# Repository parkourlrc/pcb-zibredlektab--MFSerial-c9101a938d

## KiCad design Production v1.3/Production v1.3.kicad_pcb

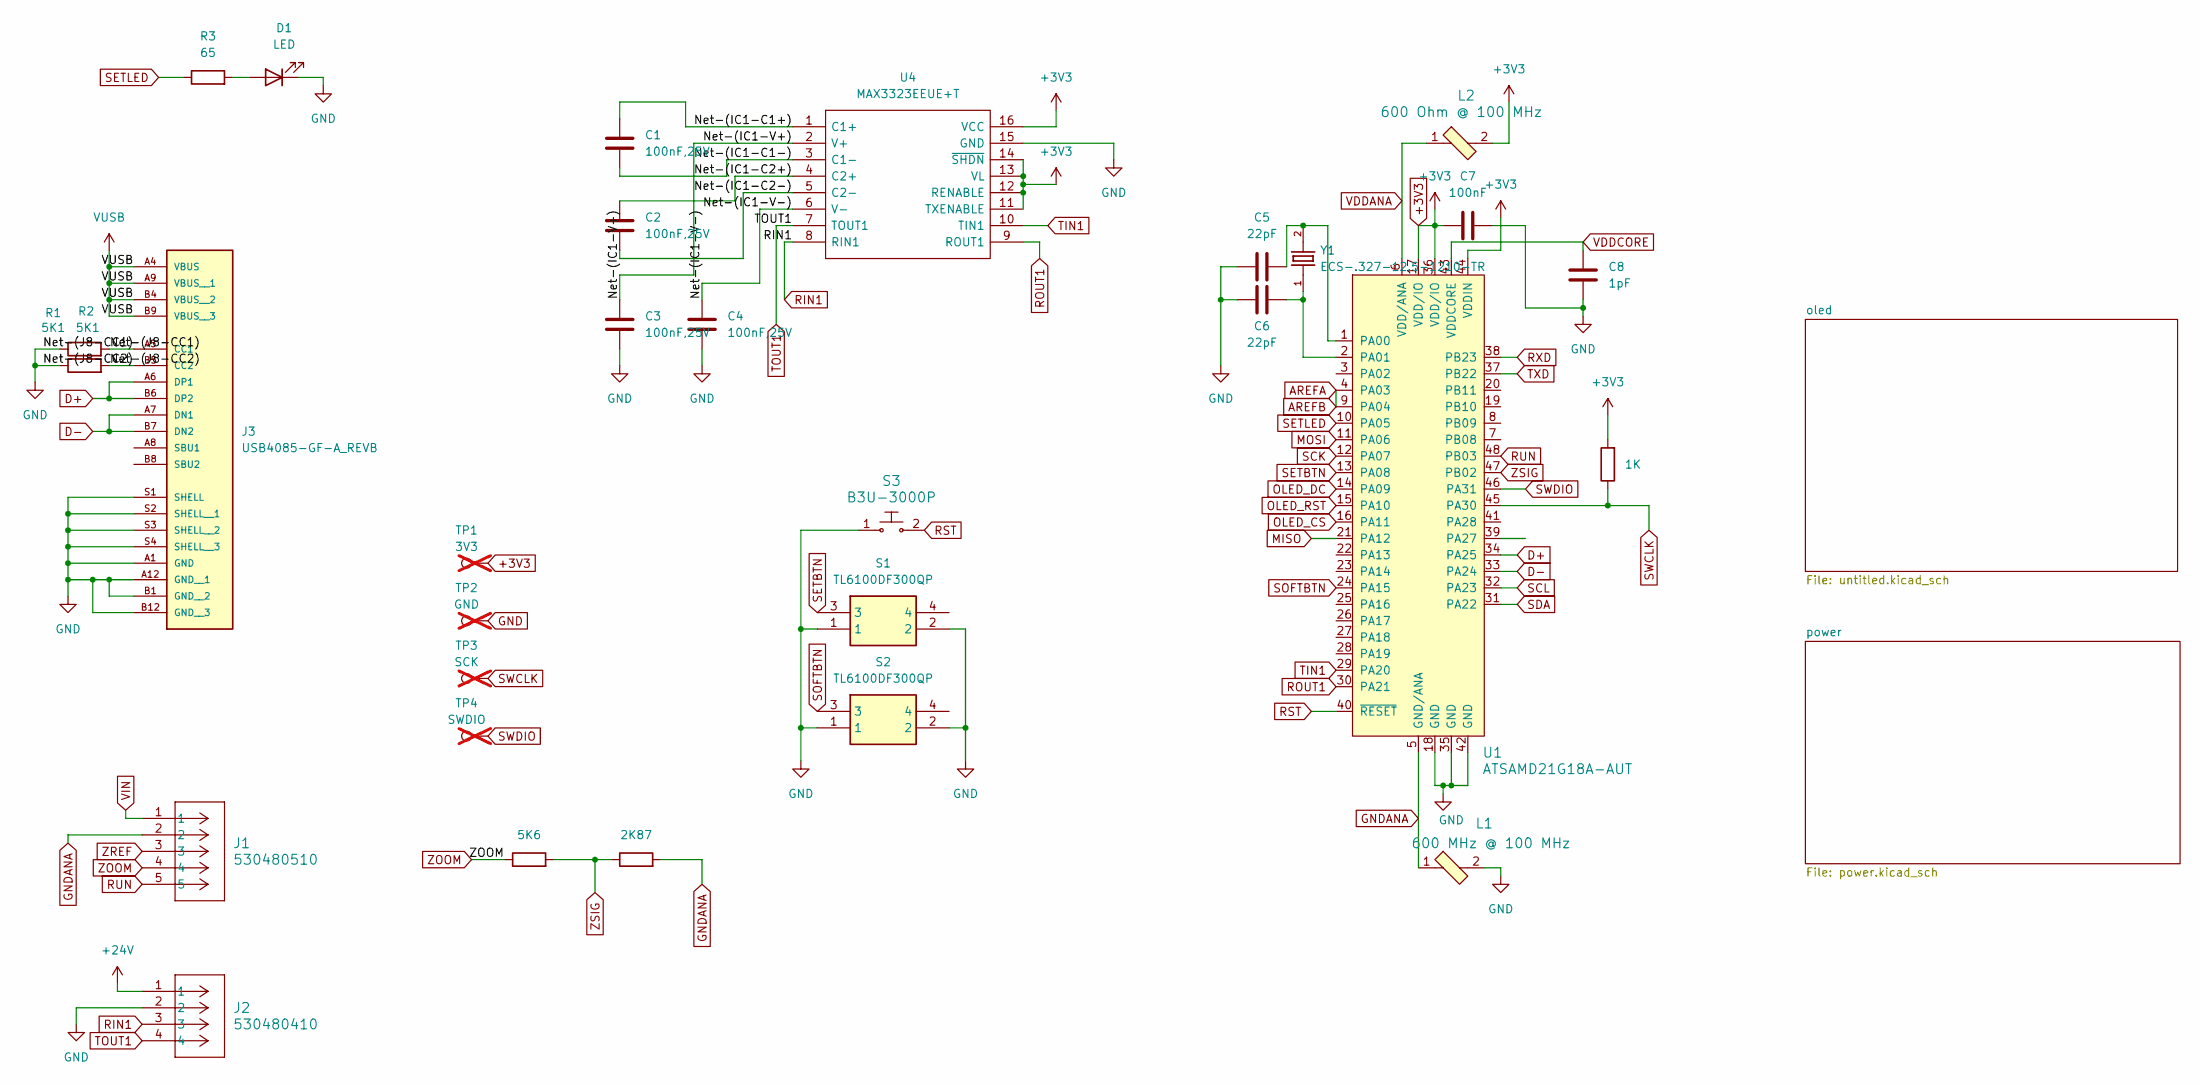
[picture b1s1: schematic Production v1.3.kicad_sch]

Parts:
C1, C2, C3, C4: 100nF,25V; C_0402_1005Metric; Part Number CL05B104KA5NNNC
C5, C6: 22pF; C_0402_1005Metric; Part Number CL05C220JB51PNC
C7: 100nF; C_0402_1005Metric; Part Number CL05B104KA5NNNC
C8: 1pF; C_0402_1005Metric; Part Number CL05C010CB5NNNC
D1: LED; LED_0805_2012Metric; Part Number B1701URO-20D000114U1930
J1: 530480510; Molex_PicoBlade_53048-0510_1x05_P1.25mm_Horizontal; Part Number 530480510
J2: 530480410; Molex_PicoBlade_53048-0410_1x04_P1.25mm_Horizontal; Part Number 530480410
J3: USB4085-GF-A_REVB; CONN16_USB4085-GF-A_GCT; Part Number USB4085-GF-A
L1: 600 MHz @ 100 MHz; 0603; Part Number 74269262601
L2: 600 Ohm @ 100 MHz; 0603; Part Number 74269262601
R1, R2: 5K1; R_0201_0603Metric; Part Number ERJ-1GNF5101C
R3: 65; R_0201_0603Metric; Part Number ERJ-1GNF64R9C
R4: 5K6; R_0402_1005Metric; Part Number ERA-2VRW5601X
R5: 2K87; R_0402_1005Metric; Part Number ERA-2AEB2871X
R6: 1K; R_0201_0603Metric; Part Number RC0201FR-071KL
S1, S2: TL6100DF300QP; TL6100DF160QP; Part Number TL6100DF300QP
S3: B3U-3000P; SW_SPST_B3U-3000P; Part Number B3U-3000P
TP1: 3V3; PinHeader_1x01_P1.27mm_Vertical; not fitted
TP2: GND; PinHeader_1x01_P1.27mm_Vertical; not fitted
TP3: SCK; PinHeader_1x01_P1.27mm_Vertical; not fitted
TP4: SWDIO; PinHeader_1x01_P1.27mm_Vertical; not fitted
U1: ATSAMD21G18A-AUT; TQFP-48_7x7mm_P0.5mm; Part Number ATSAMD21G18A-AUT
U4: MAX3323EEUE+T; TSSOP-16_4.4x5mm_P0.65mm; Part Number MAX3323EEUE+T
Y1: ECS-.327-12.5-1210-TR; XTAL_ECS-.327-12.5-1210-TR; Part Number ECS-.327-12.5-1210-TR

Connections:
+3V3: C7.1, L2.2, R6.2, TP1.1, U1.17 (VDD/IO), U1.36 (VDD/IO), U1.44 (VDDIN), U4.11 (TXENABLE), U4.12 (RENABLE), U4.13 (VL), U4.14 (~SHDN), U4.16 (VCC); also elsewhere on the board
+24V: J2.1; also elsewhere on the board
/Net-(IC1-C1+): C1.1, U4.1 (C1+)
/Net-(IC1-C1-): C1.2, U4.3 (C1-)
/Net-(IC1-C2+): C2.1, U4.4 (C2+)
/Net-(IC1-C2-): C2.2, U4.5 (C2-)
/Net-(IC1-V+): C3.1, U4.2 (V+)
/Net-(IC1-V-): C4.1, U4.6 (V-)
/Net-(J8-CC1): J3.A5 (CC1), R1.2
/Net-(J8-CC2): J3.B5 (CC2), R2.2
AREFA: U1.4 (PA03), U1.9 (PA04); also elsewhere on the board
D+: J3.A6 (DP1), J3.B6 (DP2), U1.34 (PA25)
D-: J3.A7 (DN1), J3.B7 (DN2), U1.33 (PA24)
GND: C3.2, C4.2, C5.1, C6.1, C7.2, C8.2, D1.1 (K), J2.2, J3.A1 (GND), J3.A12 (GND__1), J3.B1 (GND__2), J3.B12 (GND__3), J3.S1 (SHELL), J3.S2 (SHELL__1), J3.S3 (SHELL__2), J3.S4 (SHELL__3), L1.2, R1.1, R2.1, S1.1, S1.2, S2.1, S2.2, S3.1, TP2.1, U1.18 (GND), U1.35 (GND), U1.42 (GND), U4.15 (GND); also elsewhere on the board
GNDANA: J1.2, L1.1, R5.2, U1.5 (GND/ANA); also elsewhere on the board
MISO: U1.21 (PA12)
MOSI: U1.11 (PA06); also elsewhere on the board
unnamed: D1.2 (A), R3.2
unnamed: C5.2, U1.1 (PA00), Y1.2
unnamed: C6.2, U1.2 (PA01), Y1.1
OLED_CS: U1.16 (PA11); also elsewhere on the board
OLED_DC: U1.14 (PA09); also elsewhere on the board
OLED_RST: U1.15 (PA10); also elsewhere on the board
RIN1: J2.3, U4.8 (RIN1)
ROUT1: U1.30 (PA21), U4.9 (ROUT1)
RST: S3.2, U1.40 (~RESET)
RUN: J1.5, U1.48 (PB03)
RXD: U1.38 (PB23)
SCK: U1.12 (PA07); also elsewhere on the board
SCL: U1.32 (PA23)
SDA: U1.31 (PA22)
SETBTN: S1.3, U1.13 (PA08)
SETLED: R3.1, U1.10 (PA05)
SOFTBTN: S2.3, U1.24 (PA15)
SWCLK: R6.1, TP3.1, U1.45 (PA30)
SWDIO: TP4.1, U1.46 (PA31)
TIN1: U1.29 (PA20), U4.10 (TIN1)
TOUT1: J2.4, U4.7 (TOUT1)
TXD: U1.37 (PB22)
VDDANA: L2.1, U1.6 (VDD/ANA); also elsewhere on the board
VDDCORE: C8.1, U1.43 (VDDCORE)
VIN: J1.1; also elsewhere on the board
VUSB: J3.A4 (VBUS), J3.A9 (VBUS__1), J3.B4 (VBUS__2), J3.B9 (VBUS__3); also elsewhere on the board
ZOOM: J1.4, R4.1
ZREF: J1.3; also elsewhere on the board
ZSIG: R4.2, R5.1, U1.47 (PB02)

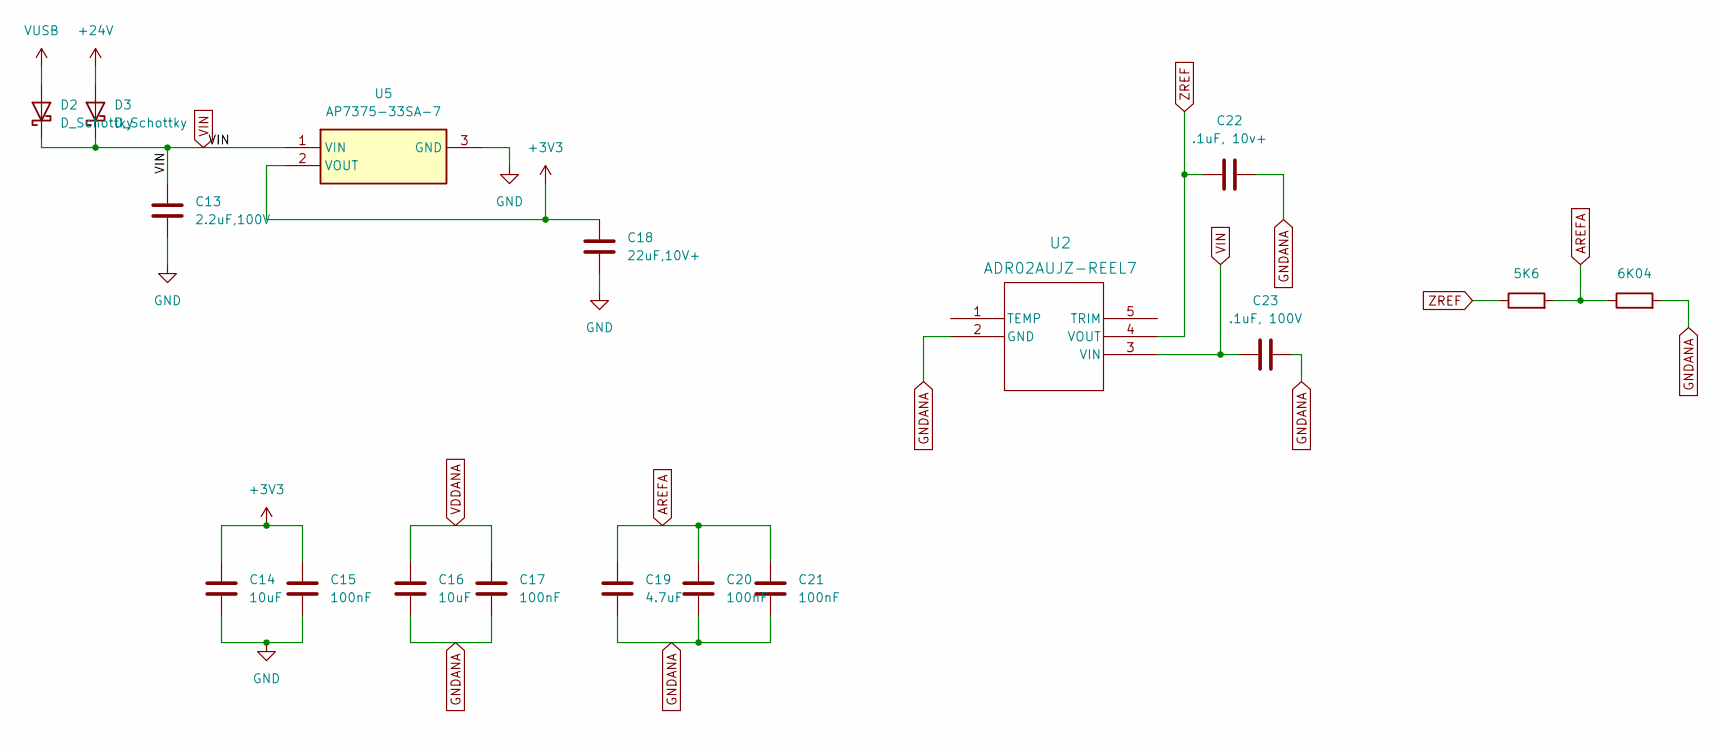
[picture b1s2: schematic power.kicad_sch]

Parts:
C13: 2.2uF,100V; C_0805_2012Metric; Part Number C2012X7R2A225K125AC
C14, C16: 10uF; C_0402_1005Metric; Part Number GRM155R61A106ME11D
C15, C17, C20, C21: 100nF; C_0402_1005Metric; Part Number CL05B104KA5NNNC
C18: 22uF,10V+; C_0402_1005Metric; Part Number GRM158R61A226ME15D
C19: 4.7uF; C_0402_1005Metric; Part Number CL05A475MP5NRNC
C22: .1uF, 10v+; C_0402_1005Metric; Part Number CL05B104KP5NNNC
C23: .1uF, 100V; C_0805_2012Metric; Part Number CL21B104KCFNNNE
D2, D3: D_Schottky; D_1206_3216Metric; Part Number SD1206S100S1R0
R9: 5K6; R_0402_1005Metric; Part Number ERA-2VRW3301X
R10: 6K04; R_0402_1005Metric; Part Number ERA-2AEB6041X
U2: ADR02AUJZ-REEL7; TSOT-23-5; Part Number ADR02AUJZ-REEL7
U5: AP7375-33SA-7; SOT96P240X110-3N; Part Number AP7375-33SA-7

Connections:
+3V3: C14.1, C15.1, C18.2, U5.2 (VOUT); also elsewhere on the board
+24V: D3.2 (A); also elsewhere on the board
AREFA: C19.1, C20.1, C21.1, R9.2, R10.1; also elsewhere on the board
GND: C13.1, C14.2, C15.2, C18.1, U5.3 (GND); also elsewhere on the board
GNDANA: C16.2, C17.2, C19.2, C20.2, C21.2, C22.1, C23.1, R10.2, U2.2 (GND); also elsewhere on the board
VDDANA: C16.1, C17.1; also elsewhere on the board
VIN: C13.2, C23.2, D2.1 (K), D3.1 (K), U2.3 (VIN), U5.1 (VIN); also elsewhere on the board
VUSB: D2.2 (A); also elsewhere on the board
ZREF: C22.2, R9.1, U2.4 (VOUT); also elsewhere on the board

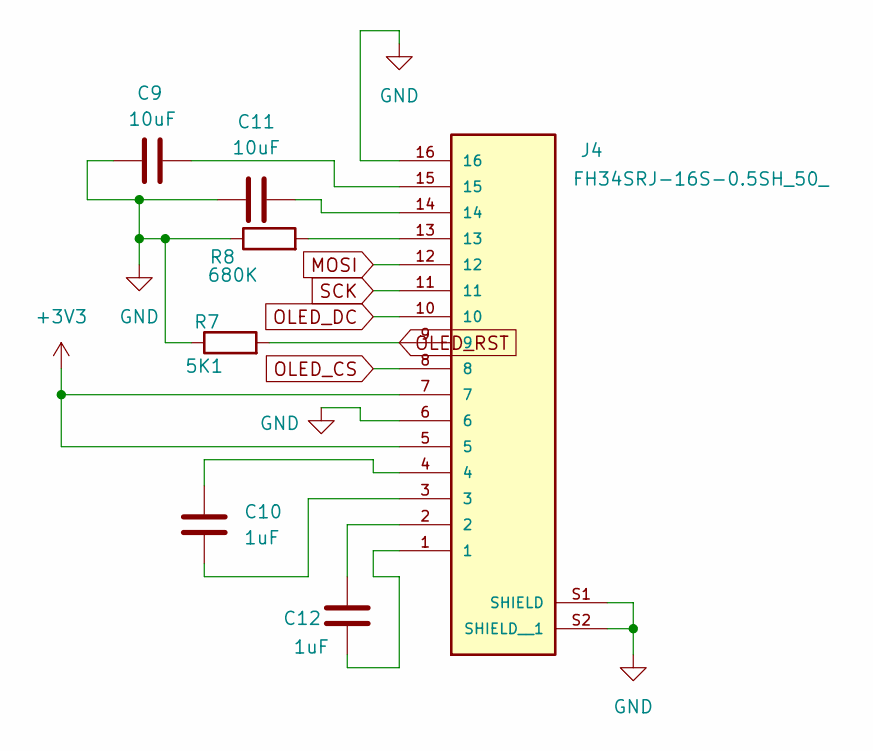
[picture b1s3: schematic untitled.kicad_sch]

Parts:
C9, C11: 10uF; C_0603_1608Metric; Part Number CL10A106KQ8NNNL
C10, C12: 1uF; C_0603_1608Metric; Part Number CL10B105KP8NNNC
J4: FH34SRJ-16S-0.5SH_50_; HRS_FH34SRJ-16S-0.5SH_50_; Part Number FH34SRJ-16S-0.5SH(50)
R7: 5K1; R_0201_0603Metric; Part Number ERJ-1GNF5101C
R8: 680K; R_0201_0603Metric; Part Number ERJ-1GNF6803C

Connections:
+3V3: J4.5, J4.7; also elsewhere on the board
GND: C9.1, C11.2, J4.6, J4.16, J4.S1 (SHIELD), J4.S2 (SHIELD__1), R7.1, R8.1; also elsewhere on the board
MOSI: J4.12; also elsewhere on the board
unnamed: C9.2, J4.15
unnamed: C10.1, J4.3
unnamed: C10.2, J4.4
unnamed: C11.1, J4.14
unnamed: C12.1, J4.1
unnamed: C12.2, J4.2
unnamed: J4.13, R8.2
OLED_CS: J4.8; also elsewhere on the board
OLED_DC: J4.10; also elsewhere on the board
OLED_RST: J4.9, R7.2; also elsewhere on the board
SCK: J4.11; also elsewhere on the board

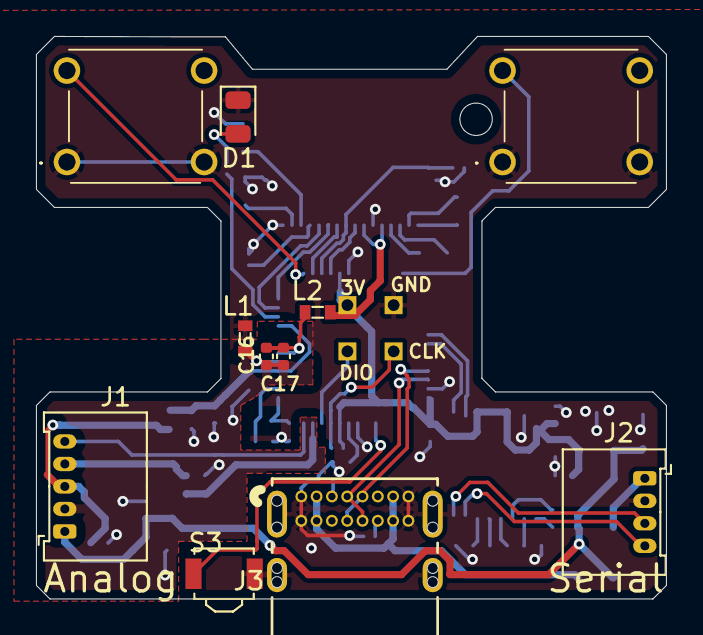
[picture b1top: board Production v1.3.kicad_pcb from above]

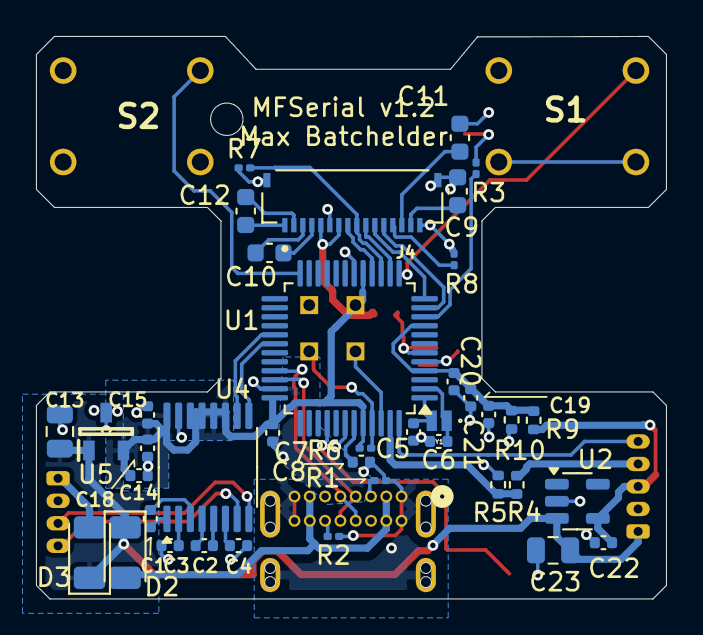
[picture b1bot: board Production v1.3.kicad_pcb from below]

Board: 2 copper layers, 35.0 x 31.2 mm, 54 parts (39 on the bottom side), 48 nets.

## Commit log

2025-10-14 Started Production v1.3 & Programmer
    Also ignored backups & binaries
